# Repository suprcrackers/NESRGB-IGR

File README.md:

# NESRGB-IGR
here you find PCBs and Codes for the NESRGB-IGR :)

If you successfully add the NESRGB-IGR you have the following functionalities available:  

Controller: Start+Select+ ...  
    - ... A+B pressed for <2s: short reset  
    - ... A+B pressed for >2s: long reset (going back to main menu if a power pak is used or in EDN8 reset to game is enabled)  
    - ... D-Pad right: Forward switching through the palette and RGB off (RGB off only available if set by jumper)  
    - ... D-Pad left: Backward switching through palette  
Reset:  
    - short push <~750ms: reset  
    - second punsh while PIC resets the NES/FC: reset as long long as button is held  
    - keeping pressed: forward switching through the palette and RGB off with delay of ~750ms for each palette   

Please note that one is not allowed to connect the PIC directly to the NESRGB.  
If you do so, the CPLD on the NESRGB will be destroyed because the PIC running with NESRGB-IGR-code is designed to run with +5V.  
I recommend to use a 74LVX125 running with 3.3V in between - this IC allows inputs up to +5V.

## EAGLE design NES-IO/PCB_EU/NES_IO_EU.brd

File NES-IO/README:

NES-I/O
========

an idea by Arcade-TV from circuit-board.de :) Thank you very much!!!

The board replaces the silver box in NES frontloader. On this PCB the following components are included:

- AC input jack
- AC to DC conversion
- MultiAV (SNES and GC(*) are supported) 
- PIC16F684 microcontroller to control the NESRGB color palette and reset the console using your controller :D

All components you need are stated on the silkscreen. An complete overview as well as an English installation guide is coming soon ;)

Grab the firmware for the PIC16F684 here: https://github.com/borti4938/Switchless-Mods/tree/master/NES/IGR_for_NESRGB/
- current version: use the 'normal version' and flash the nesrgb_igr_684_var_led.hex
- oldest PCB version (with three 10k resistors next to the 74*125): use the 'risky version' and flash nesrgb_igr_684_risky_var_led.hex

(*) 3d-printed Helder/Buffalowing connector on assemblergames (http://assemblergames.com/l/threads/f-s-nes-top-loader-snes-style-multi-a-v-socket.50494/) also fits  
    thanks for figuring out, splits (shmups forum)

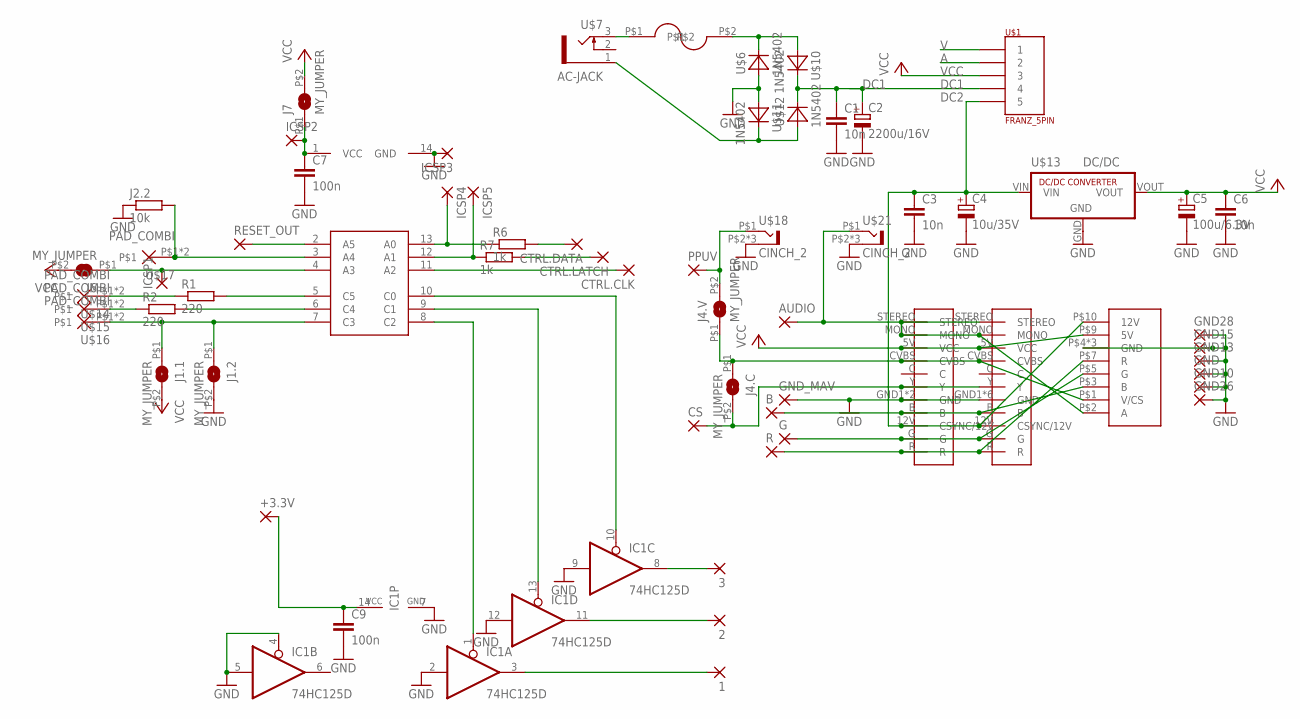
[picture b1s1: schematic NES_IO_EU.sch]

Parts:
1, 2, 3: SMD2; SMD1,27-2,54
+3.3V: SMD2; SMD1,27-2,54
AUDIO: SMD2; SMD1,27-2,54
B: SMD2; SMD1,27-2,54
C1, C3, C6: 10n; Z0805
C2: 2200u/16V; E5-13
C4: 10u/35V; PANASONIC_B
C5: 100u/6.3V; PANASONIC_D
C7, C9: 100n; Z0805
CS: SMD2; SMD1,27-2,54
CTRL.CLK, CTRL.DATA, CTRL.LATCH: SMD2; SMD1,27-2,54
G: SMD2; SMD1,27-2,54
GND, GND10, GND13, GND15, GND26, GND28: SMD5; SMD2,54-5,08
GND_MAV: SMD2; SMD1,27-2,54
IC1: 74HC125D; SO14
ICSP1, ICSP2, ICSP3, ICSP4, ICSP5: 1,6/0,8
J1.1, J1.2, J4.C, J4.V, J6, J7: MY_JUMPER; MYJUMP
J2.2: 10k; Z0805
PPUV: SMD2; SMD1,27-2,54
R: SMD2; SMD1,27-2,54
R1, R2: 220; Z0805
R6, R7: 1k; Z0805
RESET_OUT: SMD2; SMD1,27-2,54
U$1: FRANZ_5PIN; 5X2.22RM4
U$2: FUSEHOLDER
U$5: PIC16F630_SIMPLE; PIC16F630
U$6, U$10, U$11, U$12: 1N5402; DO201
U$7: AC-JACK
U$8: NESFR_JACK2
U$13: DC/DC; RECOM
U$14, U$15, U$16, U$17: PAD_COMBI
U$18, U$21: CINCH_2
U$19: GC-MULTIAV
U$20: SNES-MULTIAV2

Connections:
A: U$1.P$2 (2)
AC1A: U$2.P$1, U$7.3
AC1B: U$2.P$2, U$6.C, U$10.A
AC2: U$7.1 (5), U$11.C, U$12.A
DC1: C1.1, C2.+, U$1.P$4 (4), U$10.C, U$12.C
DC2: C3.1, C4.+, U$1.P$5 (5), U$8.P$10 (12V), U$13.VIN, U$19.12V (CSYNC/12V), U$20.12V (CSYNC/12V)
GND: C1.2, C2.-, C3.2, C4.-, C5.-, C6.2, C7.2, C9.2, GND.1, GND10.1, GND13.1, GND15.1, GND26.1, GND28.1, GND_MAV.1, IC1.2 (I), IC1.4 (OE), IC1.5 (I), IC1.7 (GND), IC1.9 (I), IC1.12 (I), ICSP3.1, J1.2.P$2 (2), J2.2.1, U$5.14 (GND), U$6.A, U$8.P$4 (GND), U$8.P$6 (GND), U$8.P$8 (GND), U$11.A, U$13.GND, U$18.P$2 (S), U$18.P$3 (S), U$18.P$4 (S), U$19.GND1 (GND), U$19.GND2 (GND), U$19.GND3 (GND), U$19.GND4 (GND), U$19.GND5 (GND), U$19.GND6 (GND), U$20.GND1 (GND), U$20.GND2 (GND), U$21.P$2 (S), U$21.P$3 (S), U$21.P$4 (S)
unnamed: AUDIO.1, U$8.P$2 (A), U$19.MONO, U$19.STEREO, U$20.MONO, U$20.STEREO, U$21.P$1 (T)
unnamed: B.1, U$8.P$3 (B), U$19.B, U$20.B
unnamed: CS.1, J4.C.P$2 (2), U$19.Y, U$20.Y
unnamed: G.1, U$8.P$5 (G), U$19.G, U$20.G
unnamed: R.1, U$8.P$7 (R), U$19.R, U$20.R
unnamed: 3.1, IC1.8 (O)
unnamed: J2.2.2, U$5.3 (A4), U$17.P$1, U$17.P$2
unnamed: R1.2, U$5.5 (C5)
unnamed: R2.2, U$5.6 (C4)
unnamed: R1.1, U$14.P$1, U$14.P$2
unnamed: R2.1, U$15.P$1, U$15.P$2
unnamed: J1.1.P$1 (1), J1.2.P$1 (1), U$5.7 (C3), U$16.P$1, U$16.P$2
unnamed: CTRL.DATA.1, R6.2
unnamed: CTRL.LATCH.1, R7.2
unnamed: CTRL.CLK.1, U$5.11 (A2)
unnamed: IC1.10 (OE), U$5.10 (C0)
unnamed: IC1.13 (OE), U$5.9 (C1)
unnamed: IC1.1 (OE), U$5.8 (C2)
unnamed: +3.3V.1, C9.1, IC1.14 (VCC)
unnamed: 1.1, IC1.3 (O)
unnamed: 2.1, IC1.11 (O)
unnamed: J4.V.P$2 (2), PPUV.1, U$18.P$1 (T)
unnamed: J4.C.P$1 (1), J4.V.P$1 (1), U$8.P$1 (V/CS), U$19.CVBS, U$20.CVBS
unnamed: C7.1, ICSP2.1, J7.P$1 (1), U$5.1 (VCC)
unnamed: ICSP1.1, J6.P$1 (1), U$5.4 (A3)
unnamed: ICSP4.1, R6.1, U$5.13 (A0)
unnamed: ICSP5.1, R7.1, U$5.12 (A1)
unnamed: RESET_OUT.1, U$5.2 (A5)
V: U$1.P$1 (1)
VCC: C5.+, C6.1, J1.1.P$2 (2), J6.P$2 (2), J7.P$2 (2), U$1.P$3 (3), U$8.P$9 (5V), U$13.VOUT, U$19.5V (VCC), U$20.5V (VCC)

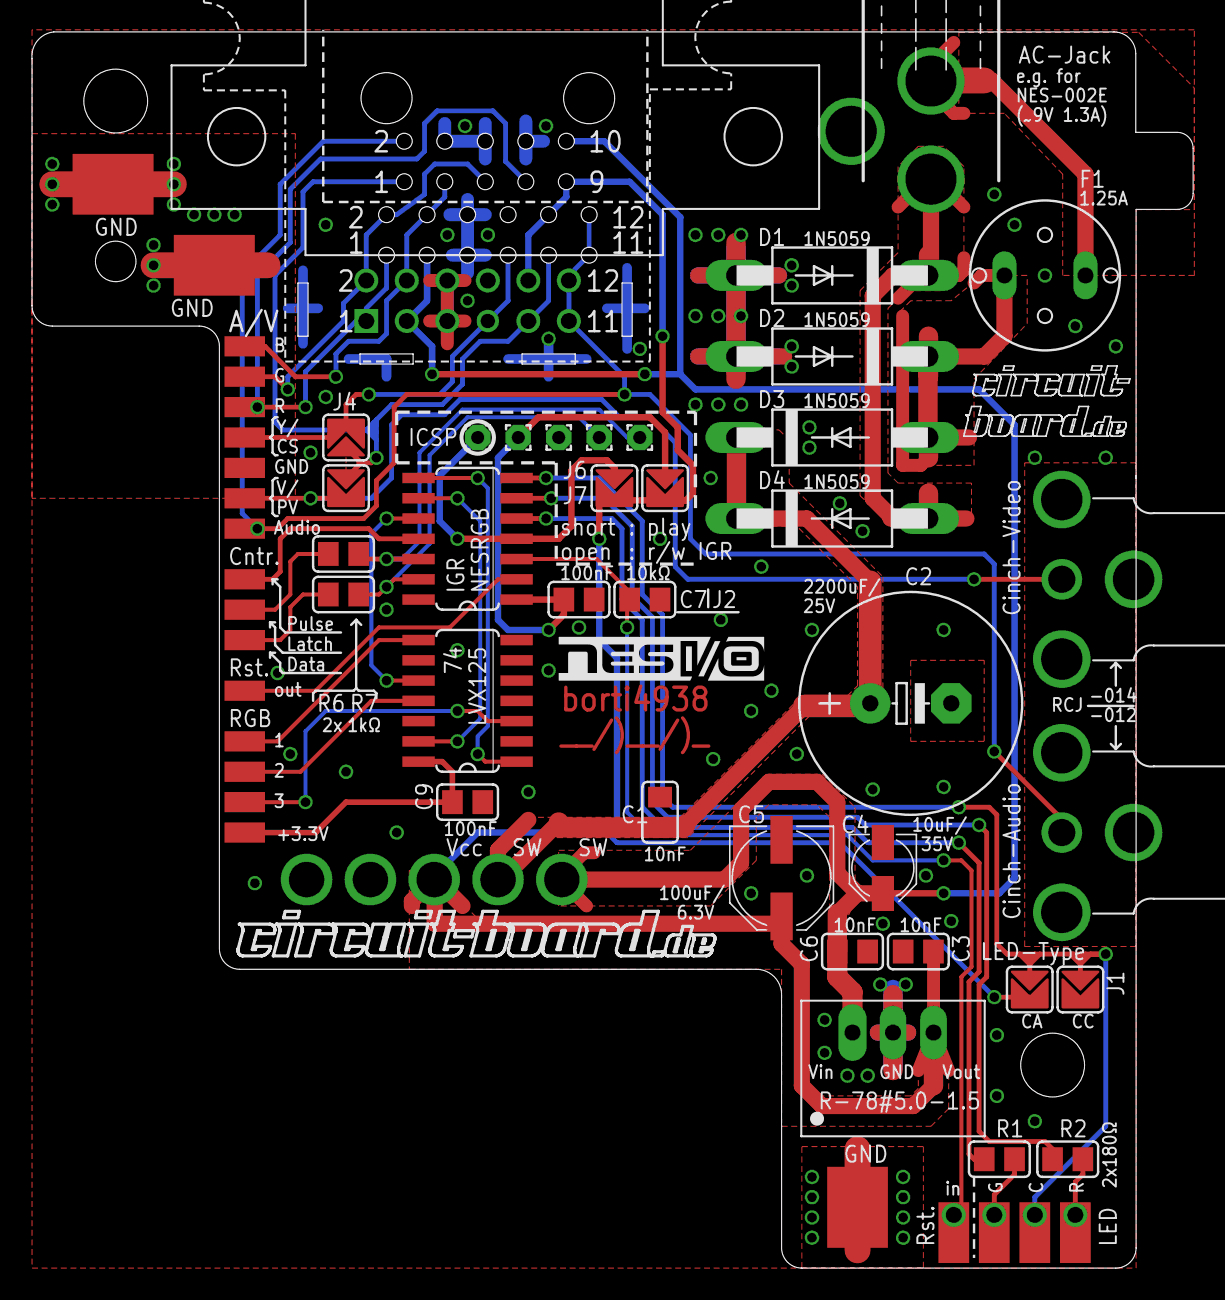
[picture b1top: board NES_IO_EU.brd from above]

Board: 2 copper layers, 72.8 x 77.5 mm, 66 parts (1 on the bottom side), 35 nets.

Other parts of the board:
U$3, U$4: NESIO-LOGO

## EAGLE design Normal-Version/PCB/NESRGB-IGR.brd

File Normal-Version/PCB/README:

Components:

IC1: PIC16F684 SOIC-14 with NESRGB-IGR code. Please choose whether you want to use a dual LED with a common anode or cathode in advance!
IC2: 74LVX125 SOIC-14

C1, C2: 100nF 0805
R1, R2: 220Ohm 0805

Jumper:

J1: 10kOhm 0805 -> set the reset type of your console there.
J2: Short the jumper you want to... '3' means that the PIC cycles only through the RGB modes; '4' als cycles through RGB off

PCB-order:

Please choose your preferred service.
You may order that PCB at OSHPark -> https://oshpark.com/shared_projects/C9jdssMN

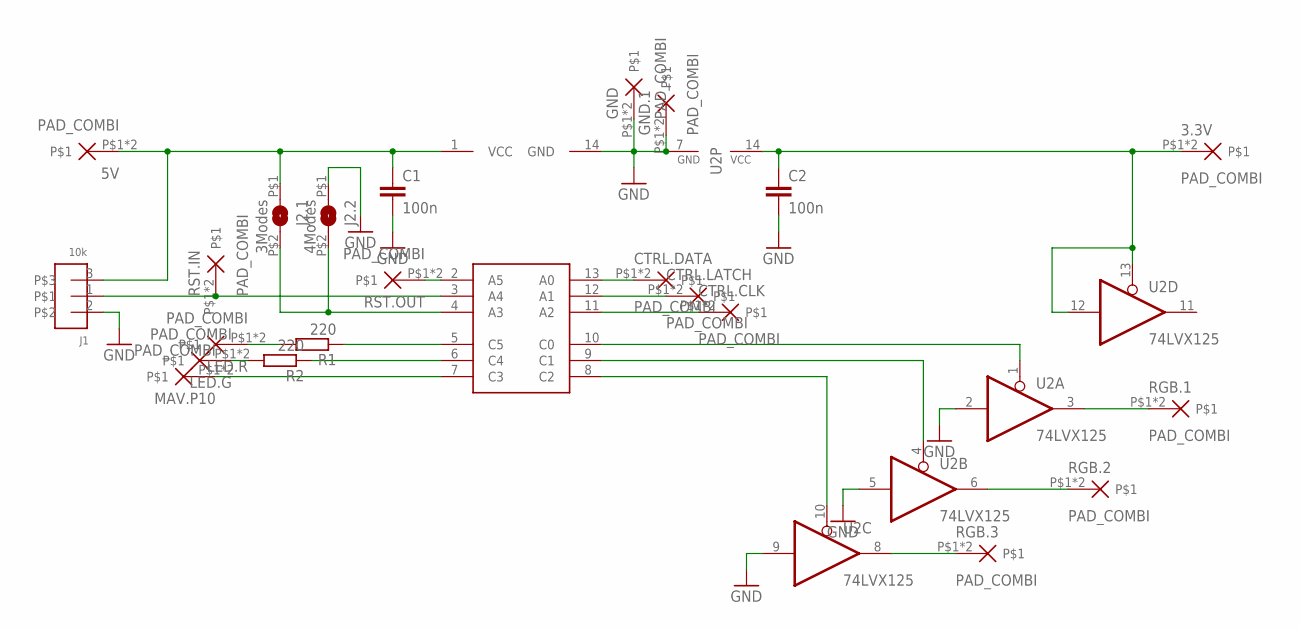
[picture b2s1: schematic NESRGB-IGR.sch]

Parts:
3.3V, 5V: PAD_COMBI
C1, C2: 100n; Z0805
CTRL.CLK, CTRL.DATA, CTRL.LATCH: PAD_COMBI
GND, GND.1: PAD_COMBI
J1: 10k; Z0805-JUMPER
J2.1: 3Modes; MYJUMP
J2.2: 4Modes; MYJUMP
LED.G, LED.R: PAD_COMBI
MAV.P10: PAD_COMBI
R1, R2: 220; Z0805
RGB.1, RGB.2, RGB.3: PAD_COMBI
RST.IN, RST.OUT: PAD_COMBI
U1: PIC16F684; PIC16F630
U2: 74LVX125; SO14

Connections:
GND: C1.2, C2.2, GND.P$1, GND.P$2, GND.1.P$1, GND.1.P$2, J1.2, J2.2.P$1 (1), U1.14 (GND), U2.2 (I), U2.5 (I), U2.7 (GND), U2.9 (I)
unnamed: J1.1, RST.IN.P$1, RST.IN.P$2, U1.3 (A4)
unnamed: 5V.P$1, 5V.P$2, C1.1, J1.3, J2.1.P$1 (1), U1.1 (VCC)
unnamed: R2.1, U1.6 (C4)
unnamed: J2.1.P$2 (2), J2.2.P$2 (2), U1.4 (A3)
unnamed: MAV.P10.P$1, MAV.P10.P$2, U1.7 (C3)
unnamed: 3.3V.P$1, 3.3V.P$2, C2.1, U2.12 (I), U2.13 (OE), U2.14 (VCC)
unnamed: CTRL.DATA.P$1, CTRL.DATA.P$2, U1.13 (A0)
unnamed: CTRL.LATCH.P$1, CTRL.LATCH.P$2, U1.12 (A1)
unnamed: CTRL.CLK.P$1, CTRL.CLK.P$2, U1.11 (A2)
unnamed: LED.G.P$1, LED.G.P$2, R2.2
unnamed: LED.R.P$1, LED.R.P$2, R1.2
unnamed: RST.OUT.P$1, RST.OUT.P$2, U1.2 (A5)
unnamed: U1.10 (C0), U2.1 (OE)
unnamed: U1.9 (C1), U2.4 (OE)
unnamed: U1.8 (C2), U2.10 (OE)
unnamed: R1.1, U1.5 (C5)
unnamed: RGB.3.P$1, RGB.3.P$2, U2.8 (O)
unnamed: RGB.2.P$1, RGB.2.P$2, U2.6 (O)
unnamed: RGB.1.P$1, RGB.1.P$2, U2.3 (O)

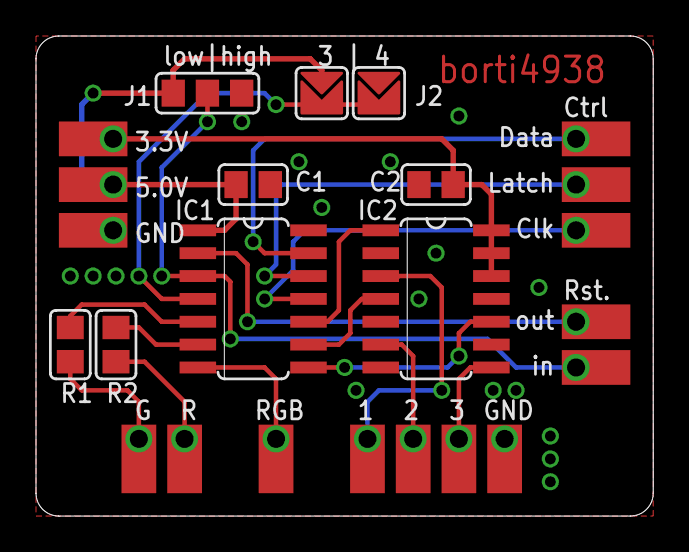
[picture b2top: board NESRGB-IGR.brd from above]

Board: 2 copper layers, 34.3 x 26.7 mm, 24 parts (0 on the bottom side), 20 nets.

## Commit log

2015-02-25 Add some description here ;)
2015-02-25 initial commit PCB
2015-02-25 initial commit Code
2015-02-25 description
2015-02-25 initial commit NES-I/O
2015-03-10 pictures for installation (pics taken from the front loader)
2015-05-27 Add gitignore
2015-05-27 code for the PIC 16F684 microcontroller modified for the NES-I/O
2015-05-27 Installation manual (GERMAN only)
2015-05-27 some detailed pictures of the installation
2015-05-27 [WIP] NES-I/O design with the RGB-output jack of the France version of the NES
2015-05-27 Add eagle design NES-I/O
2015-06-15 revert a small meaningless error (by an coding error RGB was switched off everytime a reset was requested by controller for a short moment)
2015-08-04 Add English installation manual This is a very first version. If you find typos or anything else which is hardly to understand, please write me ;)
2015-09-25 Code Update
2015-09-25 Code Update for NES-I/O 1st Batch Version
2015-09-28 rename variables (DPAD-axes)
2015-09-28 new controller reading strategy; back to the roots - change controller button bit on falling edge (interrupt steered) - sample bit ~1.5us after rising edge
2015-09-28 start into controller read similar to SNES-version; revert tabs to spaces
2015-10-08 Huge code clean up with minor improvements: - clean up code - set interrupt flags on demand - start controller reading using global interrupt - revert small mistake introduced with last commit at pre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
2015-12-20 Common design for MultiAV (from SNES or GC) and FR-NES-RGB jack
2015-12-20 Gerber Files for NES-I/O (EU)
2015-12-28 Update PCB and its name (EU version)
2015-12-28 Update file
2015-12-28 add info file for the fr rgb jack
2015-12-28 Add US version of the NES-I/O difference to the NES-I/O (EU) is only the pinout of the MultiAV (see info file)
2015-12-28 update Gerber files
2015-12-28 add gerber files for the US version of the NES-I/O
2016-02-27 update comment section
2016-02-27 shorten ctrl-reading ISR code using two macros (better to read, no functional changes)
2016-02-27 remove fixed code structure where it is not needed
2016-02-27 shorten init code (TRISA is set to default anyway)
2016-02-27 enable weak pull-up at reset line to console if low-active is detected Some CPUs (especially those in Twin Famicoms) seems to not have an internal weak pull-up (WPU). Without the PICs WPU, one has to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
2016-02-27 Hex files for the last changes
2016-04-22 remove firmware for the PIC (can be grabbed in another repository)
2016-04-22 Update PCB files
2017-10-05 update readme (what I've done a long time ago but never committed)
2017-12-27 Add LICENSE
2019-01-14 adaptation
